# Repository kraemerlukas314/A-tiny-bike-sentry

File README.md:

# A Tiny Bike Sentry

[🇩🇪 Deutsch](#-deutsch) | [🇬🇧 English](#-english)

---

## 📌 Deutsch

### Überblick
A Tiny Bike Sentry ist ein elektronisches Fahrradschloss, das bei Erschütterungen einen optischen und akustischen Alarm auslöst, um Diebstähle zu verhindern. Es basiert auf einem stromsparenden ATtiny85-Mikrocontroller und verwendet eine LED, einen Buzzer, einen Taster und einen Erschütterungssensor.

### Funktionen
- **Erschütterungserkennung**: Erkennt Bewegung mit einem Piezoelement und löst einen Alarm aus.
- **Akustische & optische Warnsignale**: Alarmiert mit einem Buzzer und einer LED.
- **Energiesparmodus**: Minimiert Stromverbrauch durch effiziente Software- und Hardwarearchitektur.
- **Manuelle Aktivierung**: Aktivierung und Deaktivierung per Knopfdruck.

### Hardware
- Mikrocontroller: **ATtiny85** (niedriger Stromverbrauch, kompakte Größe)
- Sensoren: **Piezoelement** zur Erschütterungserkennung
- Aktoren: **LED und Buzzer** zur Alarmierung
- Stromversorgung: **Akku- oder Batteriebetrieb** (optimiert für lange Laufzeit)

### Software
Die Software wurde in **C++** geschrieben und basiert auf einer **zustandsbasierten Programmierung**.
Wichtige Dateien:
- [`main.ino`](src/main/main.ino): Hauptprogramm mit der Zustandsmaschine
- [`Gpio.h`](src/main/Gpio.h) / [`Gpio.cpp`](src/main/Gpio.cpp): Steuerung der Hardware-Pins
- [`Animation.h`](src/main/Animation.h) / [`Animation.cpp`](src/main/Animation.cpp): Verwaltung der LED- und Buzzer-Signale
- [`Timing.h`](src/main/Timing.h) / [`Timing.cpp`](src/main/Timing.cpp): Optimierung der Zeitsteuerung
- [`defines.h`](src/main/defines.h): Konfigurationsdatei mit Schwellenwerten & Pin-Belegung

### Zustandsdiagramm
Das System arbeitet mit einer **Finite State Machine**:
- **Deep Sleep**: Gerät inaktiv, wartet auf Aktivierung
- **Sentry**: Gerät ist scharfgestellt und prüft auf Erschütterungen
- **Attention**: Vorwarnung nach erster Erschütterung
- **Alarm**: Vollständiger Alarmmodus
- **Cooldown**: Nach einer bestimmten Zeit ohne weitere Bewegung geht das System zurück in den Sentry-Modus

(Siehe [`State Machine Graph.pdf`](docs/final%20pdfs/State%20Machine%20Graph.pdf) für visuelle Darstellung)

### Installation & Nutzung
#### Voraussetzungen
- **Arduino IDE oder CLI**
- **ATtiny85 Board-Treiber** (via Board Manager installieren)
- **Arduino as ISP Programmer**

#### Kompilieren & Hochladen
1. ATtiny85 als Board in der Arduino IDE auswählen
2. `Programmer: Arduino as ISP` einstellen
3. Sketch mit `Sketch -> Hochladen über Programmer` übertragen
4. Gerät mit Strom versorgen und testen

### Dokumentation
Detaillierte Informationen zur Implementierung sind in folgenden Dateien enthalten:
- [`Benutzerdokumentation.pdf`](docs/final%20pdfs/A%20tiny%20bike%20sentry%20-%20Benutzerdokumentation.pdf): Anleitung für Endnutzer
- [`Entwicklerdokumentation.pdf`](docs/final%20pdfs/A%20tiny%20bike%20sentry%20-%20Entwicklerdokumentation.pdf): Technische Details & Implementierung
- [`Doxygen refman.pdf`](docs/final%20pdfs/Doxygen%20refman.pdf): Generierte Code-Dokumentation
- [`Präsentation.pdf`](docs/final%20pdfs/A%20tiny%20bike%20sentry%20-%20Präsentation.pdf): Überblick und Projektvorstellung

### Weiterentwicklung
- Implementierung eines **Bluetooth-Moduls** zur Fernsteuerung
- **Akkubetrieb mit Ladeschaltung** für mehr Flexibilität
- **Erweiterte Sicherheitsmechanismen** (z. B. Code-Eingabe oder Smartphone-Authentifizierung)

### Lizenz
Dieses Projekt steht unter der **MIT-Lizenz** – freie Nutzung und Modifikation sind erlaubt.

---

## 📌 English

### Overview
A Tiny Bike Sentry is an electronic bike lock that triggers an optical and acoustic alarm when vibrations are detected, helping to prevent theft. It is based on a low-power ATtiny85 microcontroller and uses an LED, a buzzer, a button, and a vibration sensor.

### Features
- **Vibration detection**: Detects movement with a piezo element and triggers an alarm.
- **Acoustic & optical warning signals**: Alerts with a buzzer and LED.
- **Energy-saving mode**: Minimizes power consumption through an efficient software and hardware architecture.
- **Manual activation**: Activate and deactivate via a button press.

### Hardware
- Microcontroller: **ATtiny85** (low power consumption, compact size)
- Sensors: **Piezo element** for vibration detection
- Actuators: **LED and buzzer** for alarming
- Power supply: **Battery or rechargeable operation** (optimized for long battery life)

### Software
The software is written in **C++** and is based on a **state-based programming** approach.
Key files:
- [`main.ino`](src/main/main.ino): Main program with the state machine
- [`Gpio.h`](src/main/Gpio.h) / [`Gpio.cpp`](src/main/Gpio.cpp): Controls hardware pins
- [`Animation.h`](src/main/Animation.h) / [`Animation.cpp`](src/main/Animation.cpp): Manages LED and buzzer signals
- [`Timing.h`](src/main/Timing.h) / [`Timing.cpp`](src/main/Timing.cpp): Optimizes time control
- [`defines.h`](src/main/defines.h): Configuration file with thresholds & pin assignments

### State Diagram
The system operates with a **Finite State Machine**:
- **Deep Sleep**: Device is inactive, waiting for activation
- **Sentry**: Device is armed and checking for vibrations
- **Attention**: Pre-warning after initial vibration detection
- **Alarm**: Full alarm mode
- **Cooldown**: After a certain time without further movement, the system returns to the Sentry mode

(See [`State Machine Graph.pdf`](docs/final%20pdfs/State%20Machine%20Graph.pdf) for a visual representation)

### Installation & Usage
#### Requirements
- **Arduino IDE or CLI**
- **ATtiny85 board driver** (install via board manager)
- **Arduino as ISP programmer**

#### Compiling & Uploading
1. Select ATtiny85 as board in Arduino IDE
2. Set `Programmer: Arduino as ISP`
3. Upload the sketch using `Sketch -> Upload Using Programmer`
4. Power the device and test

### Documentation
Detailed implementation information can be found in the following files:
- [`Benutzerdokumentation.pdf`](docs/final%20pdfs/A%20tiny%20bike%20sentry%20-%20Benutzerdokumentation.pdf): User manual
- [`Entwicklerdokumentation.pdf`](docs/final%20pdfs/A%20tiny%20bike%20sentry%20-%20Entwicklerdokumentation.pdf): Technical details & implementation
- [`Doxygen refman.pdf`](docs/final%20pdfs/Doxygen%20refman.pdf): Generated code documentation
- [`Präsentation.pdf`](docs/final%20pdfs/A%20tiny%20bike%20sentry%20-%20Präsentation.pdf): Overview and project presentation

### License
This project is released under the **MIT License** – free to use and modify.

---

**Project by Lukas Krämer | Winter Semester 2024**  
[GitHub Repository](https://github.com/kraemerlukas314/A-tiny-bike-sentry)

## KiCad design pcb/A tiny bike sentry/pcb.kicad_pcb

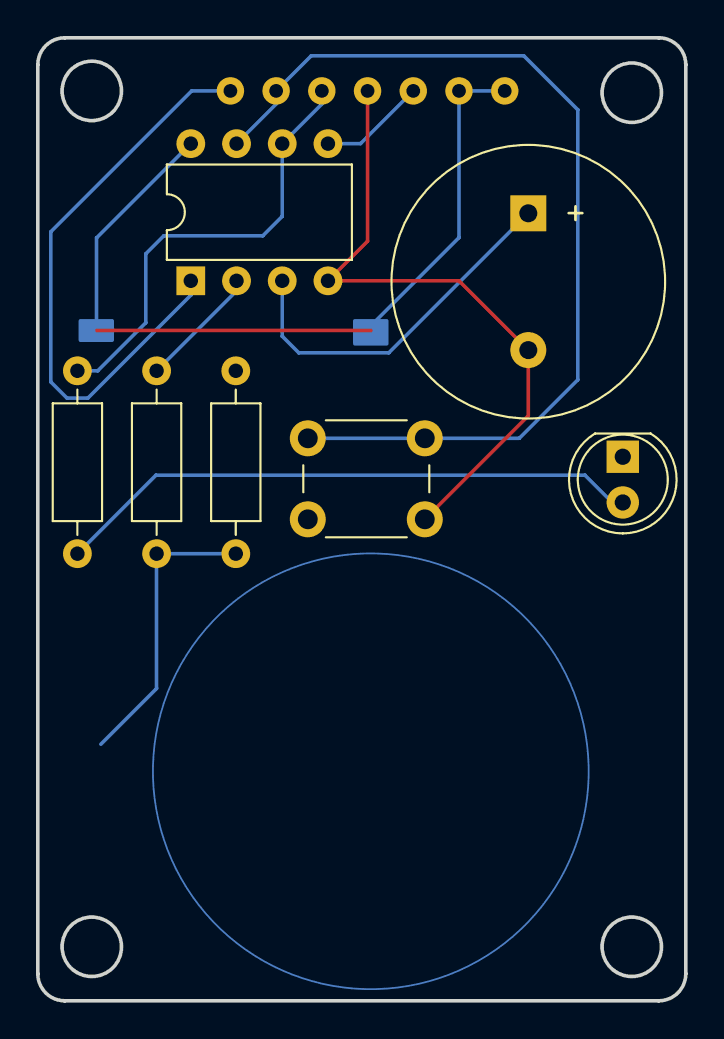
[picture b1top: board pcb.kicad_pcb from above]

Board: 2 copper layers, 36.0 x 53.5 mm, 9 parts (0 on the bottom side), 10 nets.

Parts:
BZ1: Buzzer; Buzzer_15x7.5RM7.6
D1: LED; LED_D5.0mm
R1: 10k; R_Axial_DIN0207_L6.3mm_D2.5mm_P10.16mm_Horizontal
R2: 1M; R_Axial_DIN0207_L6.3mm_D2.5mm_P10.16mm_Horizontal
R3: 220; R_Axial_DIN0207_L6.3mm_D2.5mm_P10.16mm_Horizontal
SW1: SW_Push; SW_PUSH_6mm
U1: ATtiny85-20P; DIP-8_W7.62mm
U2: Arduino_connector
U3: Piezo

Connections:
+5V: U1.8 (VCC), U2.6 (5V), U2.7 (5V)
GND: BZ1.2 (-), D1.1 (K), R2.1, SW1.2, U1.4 (GND), U2.4 (GND), U3.1 (-)
unnamed: BZ1.1 (+), U1.3 (XTAL2/PB4)
unnamed: D1.2 (A), R3.2
unnamed: U1.5 (AREF/PB0), U2.5 (ARD11)
unnamed: R3.1, U1.6 (PB1), U2.3 (ARD12)
unnamed: SW1.1, U1.7 (PB2), U2.2 (ARD13)
unnamed: R1.1, U1.2 (XTAL1/PB3)
unnamed: U1.1 (~RESET/PB5), U2.1 (ARD10)
unnamed: R1.2, R2.2, U3.2 (+)

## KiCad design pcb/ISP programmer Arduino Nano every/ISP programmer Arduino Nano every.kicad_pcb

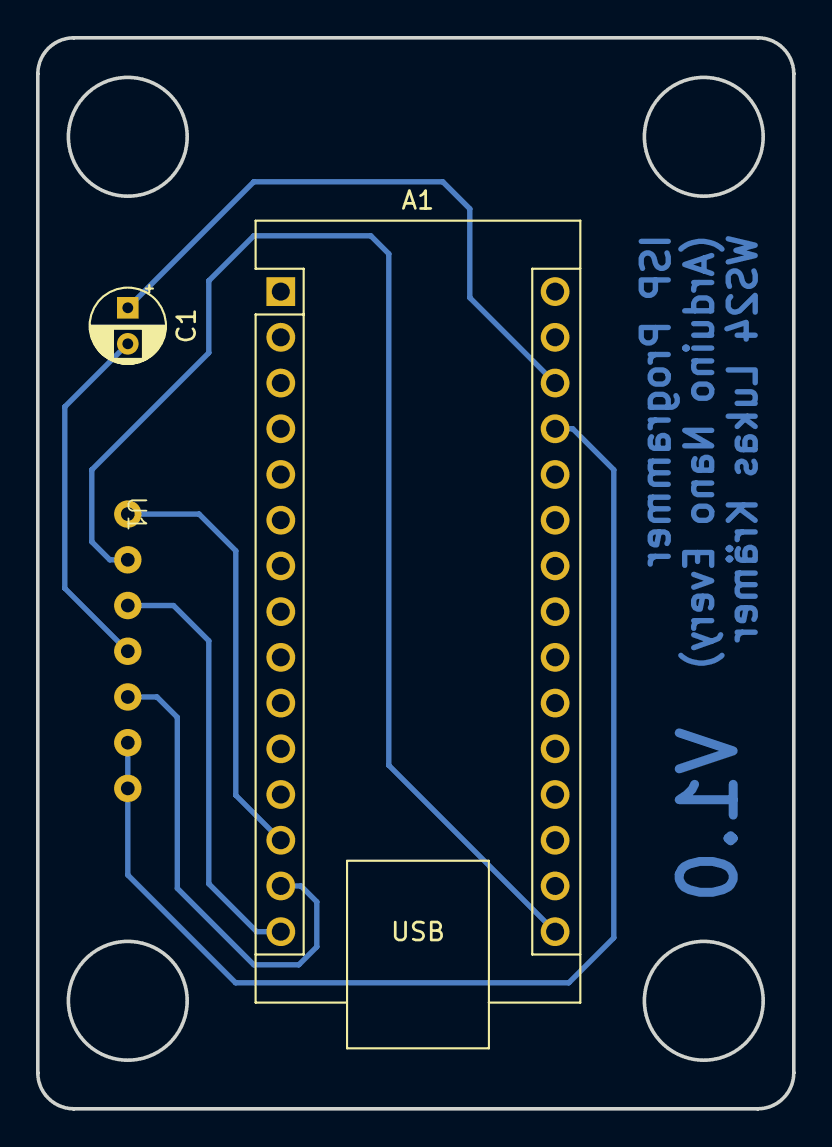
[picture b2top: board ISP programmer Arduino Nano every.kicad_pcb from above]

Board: 2 copper layers, 42.0 x 59.5 mm, 3 parts (0 on the bottom side), 7 nets.

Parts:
A1: Arduino_Nano_Every; Arduino_Nano
C1: C_Polarized; CP_Radial_D4.0mm_P2.00mm
U1: Arduino_connector

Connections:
5V: A1.27 (+5V), U1.6 (5V), U1.7 (5V)
GND: A1.29 (GND), C1.2, U1.4 (GND)
unnamed: A1.13 (D10), U1.1 (ARD10)
unnamed: A1.15 (MISO), U1.3 (ARD12)
unnamed: A1.14 (MOSI), U1.5 (ARD11)
unnamed: A1.16 (SCK), U1.2 (ARD13)
unnamed: A1.28 (~RESET), C1.1

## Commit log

2024-10-16 Add project proposal
2024-10-25 Add KiCad project
2024-10-26 Add schematic
2024-11-05 Add PCB draft
2024-11-06 Finish PCB design
2024-11-06 Add fabrication files
2024-11-10 Add ISP programmer KiCad files and gerber
2024-11-16 Add basic code structure
2024-11-17 Add button debouncing, fix piezo false positives
2024-11-18 Finish codebase draft, basic functionality with modes working
2024-11-22 Before deep sleep code
2024-11-22 Working logic
2024-11-24 Interrupts and deep sleep working
2024-11-24 Cooldowns working
2024-11-24 Watchdog working
2024-11-24 Add uploading script
2024-12-11 Add upload script for windows
2024-12-11 Add code comments, code not working
2024-12-11 Refactoring
2024-12-11 Recactor
2024-12-13 Add Animation and Timing class
2024-12-13 Finish Animation and Timing classes, program working like before changing to classes
2024-12-14 Create and use Animation::set_pin
2024-12-14 Add Animation class
2024-12-14 Use PIN_BUTTON as interrupt pin instead of hard coded name
2024-12-14 Add code comments
2024-12-14 Add doxygen config file
2024-12-15 Add Doxygen file
2024-12-15 Add make script for documentation
2024-12-19 Add first draft of Entwicklerdokumentation
2024-12-19 Add useage instructions
2025-01-08 Update docs
2025-01-20 Add docs (presentation, final pdf exports for everything else)
2025-01-20 Add proper README
2025-01-20 Add links to README
